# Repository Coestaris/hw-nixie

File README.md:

# Nixie clock

Both clock revisions and the tube docks have been manufactured and tested.

> **AI use.** The authors use AI for additional validation, component research, testbench setup and simulation, intermediate design reviews, release setup, and assistance with KiCad and 3D model edits. The authors developed the original designs and schematics manually, and other people reviewed them. The authors make the technical and visual decisions and take responsibility for them.

This USB-powered clock drives four IN-8-2 nixie tubes. Rev1 tests the boost converter. Rev2 combines the high-voltage supply, controller, and tube drivers on one motherboard. Each standalone dock carries one tube and plugs into Rev2.

## Goals and architecture

Rev1 isolates the high-voltage stage so its topology and control can be evaluated independently. An XL6007 and TDK ATB322524 transformer form the boost stage, with an MCP6001 in the control circuitry. The simulation sources document startup behavior and the limits of the behavioral models.

Rev2 adds an STM32U073 controller, four IN-8-2 docks, 74HC595 shift registers, ULN2003A arrays, and discrete high-voltage drivers. USB-C supplies the board. The MCU controls the display and the adjustable high-voltage supply.

```mermaid
flowchart LR
  USB[USB-C power] --> Boost[XL6007 high-voltage stage]
  USB --> Logic[Logic supply]
  Logic --> MCU[STM32U073]
  MCU --> Drivers[Shift registers and tube drivers]
  Boost --> Tubes[Four IN-8-2 tube docks]
  Drivers --> Tubes
  MCU --> Boost
```

## Hardware projects

| Board | Purpose | Design | Simulation |
| --- | --- | --- | --- |
| dock_rev1 | Tube carrier | [KiCad project](hardware/dock_rev1/dock_rev1.kicad_pro) | — |
| rev1 | Boost converter test board | [KiCad project](hardware/rev1/nixie_rev1.kicad_pro) | [Models, runner, and test cases](sim/rev1/) |
| rev2 | Four-tube clock motherboard | [KiCad project](hardware/rev2/nixie_rev2.kicad_pro) | [Models, runner, and test cases](sim/rev2/) |

### dock_rev1 - IN-8-2 dock

The two-layer dock carries one wire-ended IN-8-2 tube. Four 1×3, 2.54 mm sockets mate with the motherboard pin headers and carry the anode, digit cathodes, and decimal point. The assembly model includes the tube and all four sockets. [Dock release](https://github.com/Coestaris/hw-nixie/releases/tag/dock_rev1)

<details>
<summary>Top and bottom views</summary>

</details>

| File | Download |
| --- | --- |
| Schematic PDF | [dock_rev1-schematic.pdf](https://github.com/Coestaris/hw-nixie/releases/download/dock_rev1/dock_rev1-schematic.pdf) |
| PCB PDF | [dock_rev1-pcb.pdf](https://github.com/Coestaris/hw-nixie/releases/download/dock_rev1/dock_rev1-pcb.pdf) |
| Gerbers and drill files | [dock_rev1-gerbers.zip](https://github.com/Coestaris/hw-nixie/releases/download/dock_rev1/dock_rev1-gerbers.zip) |
| 3D assembly model | [dock_rev1.stpz](https://github.com/Coestaris/hw-nixie/releases/download/dock_rev1/dock_rev1.stpz) |

### rev1 - boost topology test board

Rev1 isolates the high-voltage converter and its control loop for bring-up. [Rev1 release](https://github.com/Coestaris/hw-nixie/releases/tag/rev1)

<details>
<summary>Top and bottom views</summary>

</details>

| File | Download |
| --- | --- |
| Schematic PDF | [nixie_rev1-schematic.pdf](https://github.com/Coestaris/hw-nixie/releases/download/rev1/nixie_rev1-schematic.pdf) |
| PCB PDF | [nixie_rev1-pcb.pdf](https://github.com/Coestaris/hw-nixie/releases/download/rev1/nixie_rev1-pcb.pdf) |
| Gerbers and drill files | [nixie_rev1-gerbers.zip](https://github.com/Coestaris/hw-nixie/releases/download/rev1/nixie_rev1-gerbers.zip) |
| JLCPCB BOM | [nixie_rev1-jlcpcb-bom.csv](https://github.com/Coestaris/hw-nixie/releases/download/rev1/nixie_rev1-jlcpcb-bom.csv) |
| JLCPCB placement | [nixie_rev1-jlcpcb-pnp.csv](https://github.com/Coestaris/hw-nixie/releases/download/rev1/nixie_rev1-jlcpcb-pnp.csv) |
| 3D assembly model | [nixie_rev1.stpz](https://github.com/Coestaris/hw-nixie/releases/download/rev1/nixie_rev1.stpz) |
| Simulation netlist, log, and results | [nixie_rev1-simulation.tar.gz](https://github.com/Coestaris/hw-nixie/releases/download/rev1/nixie_rev1-simulation.tar.gz) |

#### Hardware bring-up

The converter started normally, and the enable pin worked as expected. The bulk capacitor footprint limited the choice of high-voltage electrolytics. The only suitable part available for bring-up was a physically large 33 µF electrolytic, which replaced the 2.2 µF part specified in the schematic. The larger capacitance slowed the response to voltage adjustments.

#### Bench test results

- **Output voltage and ripple.** With a load equivalent to 20 kΩ (10 mA at 200 V), the output reached about 240–245 V with approximately 40–50 mV of ripple.
- **Voltage adjustment.** As the control setting increased, the output rose roughly linearly at first, then leveled off in a way that resembled an exponential approach to a limit. Under these test conditions, about 230 V was the practical upper limit for normal regulation.
- **Switching spikes.** At 245 V output, the measured spikes stayed at or below 40 V. This was considered acceptable for the transformer, so the prototype ran without a snubber.

<details>
<summary>Bring-up photos</summary>

</details>

### rev2 - clock motherboard

Rev2 supplies power and digit-drive signals to four plug-in docks. The assembly model includes the docks, their pin headers, and M2 standoffs. [Rev2 release](https://github.com/Coestaris/hw-nixie/releases/tag/rev2)

<details>
<summary>Top and bottom views</summary>

</details>

| File | Download |
| --- | --- |
| Schematic PDF | [nixie_rev2-schematic.pdf](https://github.com/Coestaris/hw-nixie/releases/download/rev2/nixie_rev2-schematic.pdf) |
| PCB PDF | [nixie_rev2-pcb.pdf](https://github.com/Coestaris/hw-nixie/releases/download/rev2/nixie_rev2-pcb.pdf) |
| Gerbers and drill files | [nixie_rev2-gerbers.zip](https://github.com/Coestaris/hw-nixie/releases/download/rev2/nixie_rev2-gerbers.zip) |
| JLCPCB BOM | [nixie_rev2-jlcpcb-bom.csv](https://github.com/Coestaris/hw-nixie/releases/download/rev2/nixie_rev2-jlcpcb-bom.csv) |
| JLCPCB placement | [nixie_rev2-jlcpcb-pnp.csv](https://github.com/Coestaris/hw-nixie/releases/download/rev2/nixie_rev2-jlcpcb-pnp.csv) |
| 3D assembly model | [nixie_rev2.stpz](https://github.com/Coestaris/hw-nixie/releases/download/rev2/nixie_rev2.stpz) |
| Simulation netlist, log, and results | [nixie_rev2-simulation.tar.gz](https://github.com/Coestaris/hw-nixie/releases/download/rev2/nixie_rev2-simulation.tar.gz) |

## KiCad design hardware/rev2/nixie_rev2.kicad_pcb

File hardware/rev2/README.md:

# Nixie clock — revision 2

This revision has a USB-powered 5 V boost supply and four IN-8-2 lamp docks. With `R3=62k`, `R4=5.1k`, and `R13=29.4k`, the nominal feedback equation gives 128.8–180.0 V for a 0–3.3 V DAC command. Component and reference tolerances can take the output beyond these endpoints; the resistor changes do not enforce a hard 180 V ceiling.

The only KiCad project is [`nixie_rev2.kicad_pro`](nixie_rev2.kicad_pro). Its schematic is PCB-linked and also contains the KiCad/ngspice model mappings, testbench includes, and default transient analysis. The [`../../sim/rev2`](../../sim/rev2) directory contains supporting behavioral models, run profiles, result notes, and analysis tools; it does not contain a second schematic or project copy.

## Current hardware state

- `N1`–`N4` use the project-local `nixie_rev2:IN-8-2_Dock` symbol and footprint. Each footprint reproduces the exact four diagonal 1×3, 2.54 mm header locations from the historical lamp-dock design; the inner lamp-solder pads remain part of the manufactured dock and are intentionally not duplicated on the motherboard.
- `Q1` uses the project-local `nixie_rev2:2N7002` symbol with KiCad's standard `Package_TO_SOT_SMD:SOT-23` footprint (`1=G`, `2=S`, `3=D`).
- `T1` is JLCPCB/LCSC `C249001`, TDK `ATB322524-0110-T000` (Extended, Production/NRND). It uses the project-local `nixie_rev2:ATB322524-0110-T000` symbol and datasheet-derived `nixie_rev2:TDK_ATB3225` footprint. Physical pins 1–4 are the primary and pins 2–3 are the secondary.
- `U1` is JLCPCB/LCSC `C5240411`, XLSEMI `XL6007E1`, using the matching 150-mil `SOIC-8_3.9x4.9mm_P1.27mm` footprint.
- `D3` is JLCPCB/LCSC `C84263`, NationStar `NCD0603R1`; its datasheet explicitly matches KiCad's pad-1-cathode LED polarity.
- `F1` is the 1206 resettable PTC JLCPCB/LCSC `C369161`, Jinrui `JK-nSMD100-16` (1 A hold, 16 V maximum).
- `R20`, `R25`, `R30`, and `R37` are 33 kΩ 1206 parts (`C137309`) feeding the digit anodes. `R38` is a 130 kΩ 1206 part (`C229306`) in the dot cathode path. At 180 V and the IN-8-2's 100 V keep-up voltage, nominal digit current is 2.42 mA and dot current is 0.49 mA. The digit resistor dissipates 0.194 W against its 0.25 W rating at 70 °C; a shorted tube exceeds that rating. The lamp may not ignite at the low end of the boost range.
- Simulation defaults are 5 V input, enable asserted at 1 ms, `MC_BOOST_CV=1.65 V`, and a 100 kΩ high-voltage load.
- The current 100 ms mid-scale startup simulation reaches about 156 V, near the 154.4 V feedback-equation target. Its modeled clamp reaches about 60.54 V. The simulation gate permits up to 65 V under an explicit 5 V user allowance; the physical XL6007 switch rating remains 60 V.

This revision has been manufactured. The following model limitations remain relevant. The TDK behavioral models remain suitable only for topology work, not efficiency or stress sign-off. Transformer polarity, saturation, winding capacitance, compensation, startup, component stress, and fault behavior still need bench verification. See [`../../sim/rev2/results/startup_midscale.md`](../../sim/rev2/results/startup_midscale.md).

## Mechanical assembly

N1–N4 each show the [dock STEP assembly](../../assets/Nixie/dock_rev1-assembly.stpz) seated on four straight 1×3, 2.54 mm male headers. The dock model has a Z offset of 11.125 mm from the Rev2 model mount plane. SolidCraft inspection of the assembled STEP confirmed the four header and socket row centers and the mating planes.

In KiCad’s 3D Viewer, enable **Show 3D Models not in POS File** (`P`) and **Show Unspecified 3D Models** (`V`) to display the mechanical references. [KiCad 3D Viewer controls](https://docs.kicad.org/10.0/en/pcbnew/pcbnew.html)

H1–H4 use [M2 × 12 female–female hex spacers](../../assets/Mechanical/Hex_Standoff_M2_L12.stpz) centered under the Ø2.2 mm mounting holes. The 12 mm length leaves 2.1 mm below the tallest modeled underside component. The [SolidCraft source](../../assets/Mechanical/Hex_Standoff_M2_L12.sc) recreates the 4 mm across-flats envelope and uses a simplified axial bore. The supplied `Spacer M2 F F 12mm.stp` from `spacers-m2-1.snapshot.3.zip` contained open surfaces. Its SHA-256 is `842bb0d11cc96b8b27d7705f7006af9b003dc60c31174bb7509f7d39eccfacad`.

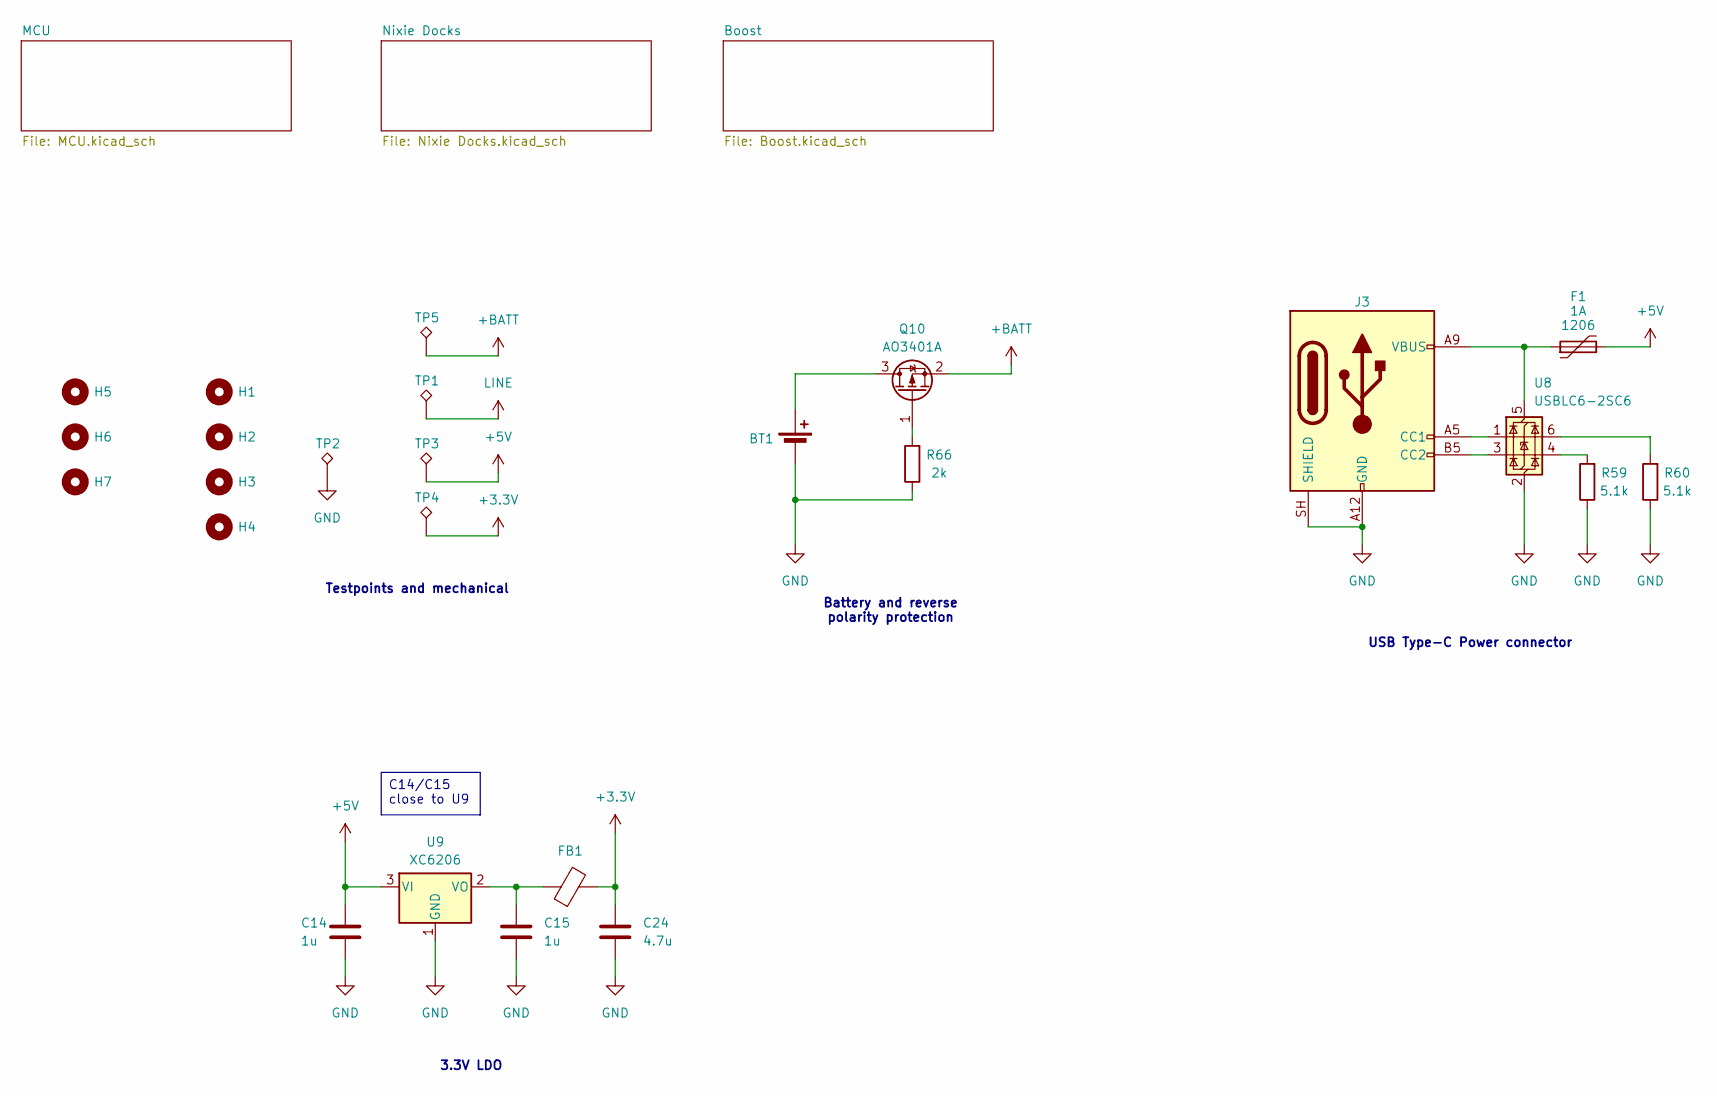
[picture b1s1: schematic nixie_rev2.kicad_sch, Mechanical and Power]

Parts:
BT1: Battery_Cell; XDCR-1220-006; Manufacturer Part Number XDCR-1220-006; LCSC Part # C7498147
C14, C15: 1u; C_0603_1608Metric; Manufacturer Part Number CC0603KRX7R6BB105; LCSC Part # C113807
C24: 4.7u; C_0603_1608Metric; Manufacturer Part Number CC0603KRX5R6BB475; LCSC Part # C109456
F1: 1A; Fuse_1206_3216Metric; Manufacturer Part Number JK-nSMD100-16; JLCPCB Part Type Extended
FB1: FerriteBead; L_0603_1608Metric; Manufacturer Part Number MPZ1608S601ATA00; LCSC Part # C107335
H1, H2, H3, H4: MountingHole; MountingHole_2.2mm_M2
H5, H6, H7: MountingHole; ToolingHole_1.152mm
J3: USB_C_Receptacle_PowerOnly_6P; USB_C_Receptacle_SHOU_HAN_TYPE-C_6P_073; Manufacturer Part Number TYPE-C 6P(073); LCSC Part # C668623
Q10: AO3401A; SOT-23; Manufacturer Part Number AO3401A; JLCPCB Part Type Basic
R59, R60: 5.1k; R_0201_0603Metric; Manufacturer Part Number RC0201JR-075K1L; LCSC Part # C163490
R66: 2k; R_0201_0603Metric; Manufacturer Part Number SC0201F2001G1BNRH; LCSC Part # C5140760
TP1, TP2, TP3, TP4, TP5: TestPoint_Alt; TestPoint_Pad_D1.0mm
U8: USBLC6-2SC6; SOT-23-6; Manufacturer Part Number USBLC6-2SC6; LCSC Part # C7519
U9: XC6206; SOT-23-3; Manufacturer Part Number XC6206P332MR; LCSC Part # C479053

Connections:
+3.3V: C24.1, FB1.2, TP4.1 (1_1); also elsewhere on the board
+5V: C14.1, F1.2, TP3.1 (1_1), U9.3 (VI); also elsewhere on the board
+BATT: Q10.2 (S), TP5.1 (1_1); also elsewhere on the board
GND: BT1.2 (-), C14.2, C15.2, C24.2, J3.A12 (GND), J3.B12 (GND), J3.SH (SHIELD), R59.1, R60.1, R66.1, TP2.1 (1_1), U8.2 (GND), U9.1 (GND); also elsewhere on the board
LINE: TP1.1 (1_1); also elsewhere on the board
unnamed: BT1.1 (+), Q10.3 (D)
unnamed: J3.A5 (CC1), U8.1 (I/O1)
unnamed: J3.B5 (CC2), U8.3 (I/O2)
unnamed: Q10.1 (G), R66.2
unnamed: R59.2, U8.4 (I/O2)
unnamed: R60.2, U8.6 (I/O1)
unnamed: F1.1, J3.A9 (VBUS), J3.B9 (VBUS), U8.5 (VBUS)
unnamed: C15.1, FB1.1, U9.2 (VO)

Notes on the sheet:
Testpoints and mechanical
3.3V LDO
USB Type-C Power connector
Battery and reverse polarity protection
C14/C15 close to U9

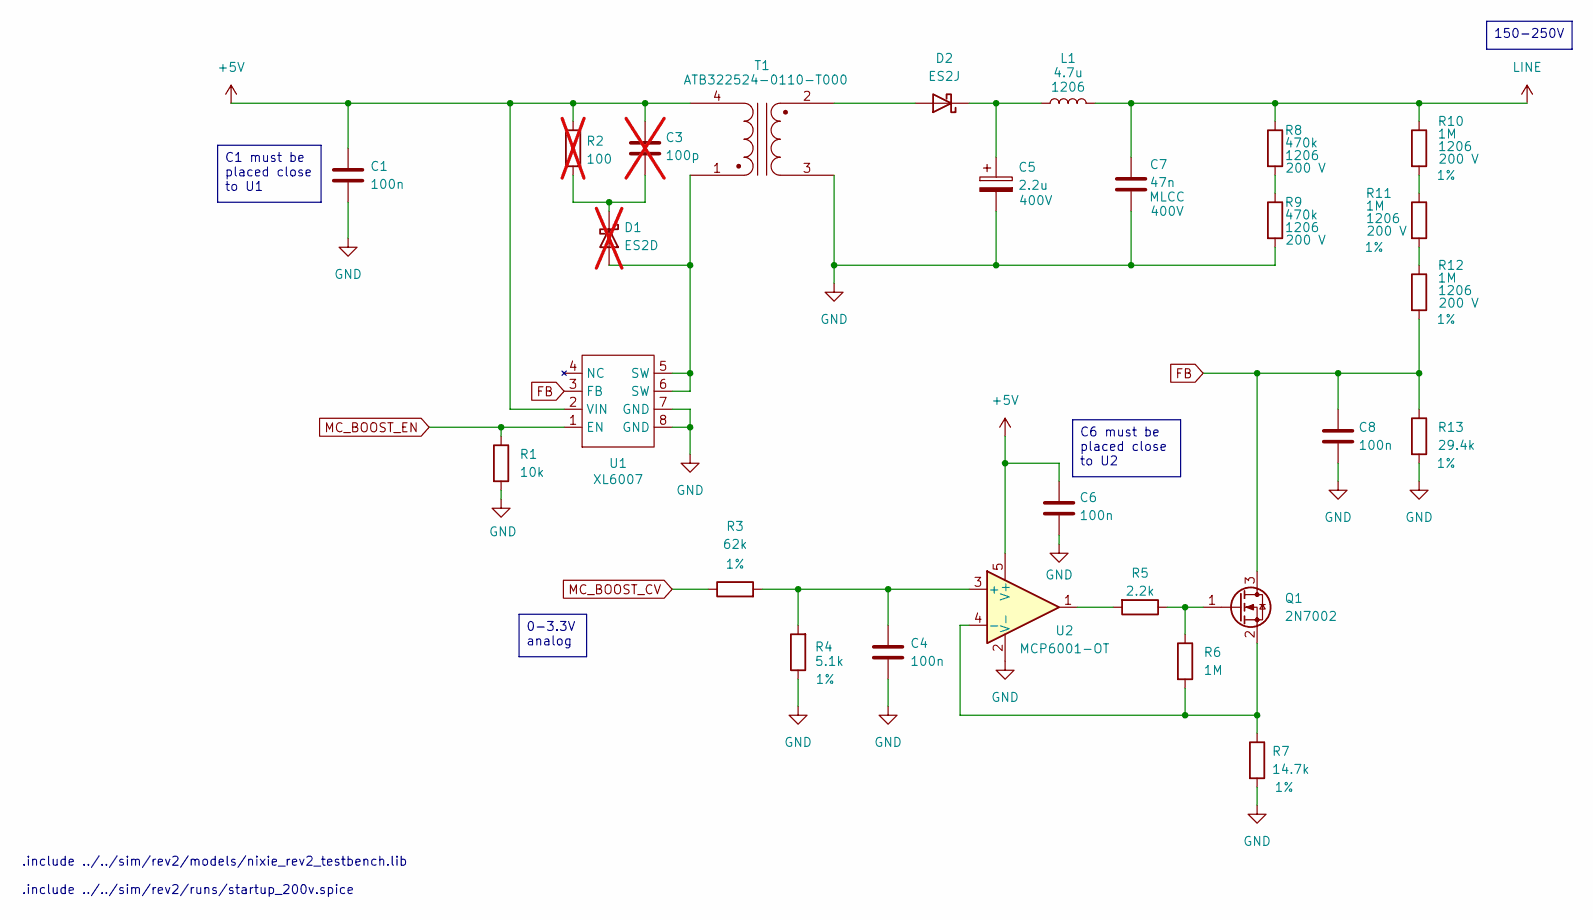
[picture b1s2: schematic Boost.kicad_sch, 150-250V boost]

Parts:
C1, C4, C6, C8: 100n; C_0201_0603Metric; Manufacturer Part Number TCC0201X7R104K100ZT; LCSC Part # C7393837
C3: 100p; C_0603_1608Metric; not fitted
C5: 2.2u; CP_Elec_6.3x9.9; Nominal Voltage 400V; Manufacturer Part Number UV2G2R2M0610; LCSC Part # C88684
C7: 47n; C_1206_3216Metric; Nominal Voltage 400V; Manufacturer Part Number TCC1206X7R473K501FT; LCSC Part # C309031
D1: ES2D; D_0603_1608Metric; not fitted
D2: ES2J; D_SMB; Manufacturer Part Number ES2JB; LCSC Part # C18199141
L1: 4.7u; L_1210_3225Metric; Manufacturer Part Number NLV32T-4R7J-EF; LCSC Part # C295128
Q1: 2N7002; SOT-23; Manufacturer Part Number 2N7002; LCSC Part # C8545
R1: 10k; R_0201_0603Metric; Manufacturer Part Number AF0201FR-0710KL; LCSC Part # C143978
R2: 100; R_0603_1608Metric; not fitted
R3: 62k; R_0201_0603Metric; Tolerance 1%; Manufacturer Part Number RC0201FR-0762KL; LCSC Part # C295812
R4: 5.1k; R_0201_0603Metric; Tolerance 1%; Manufacturer Part Number RC0201FR-075K1L; LCSC Part # C274341
R5: 2.2k; R_0201_0603Metric; Manufacturer Part Number RC0201FR-072K2L; LCSC Part # C142018
R6: 1M; R_0201_0603Metric; Manufacturer Part Number RC0201FR-071ML; LCSC Part # C295786
R7: 14.7k; R_0201_0603Metric; Tolerance 1%; Manufacturer Part Number RC0201DR-0714K7L; LCSC Part # C851654
R8, R9: 470k; R_1206_3216Metric; Nominal Voltage 200 V; Manufacturer Part Number RC1206FR-07470KL; LCSC Part # C137273
R10, R11, R12: 1M; R_1206_3216Metric; Nominal Voltage 200 V; Tolerance 1%; Manufacturer Part Number 1206W4F1004T5E; LCSC Part # C17927
R13: 29.4k; R_0603_1608Metric; Tolerance 1%; Manufacturer Part Number RC0603FR-0729K4L; LCSC Part # C137752
T1: ATB322524-0110-T000; TDK_ATB3225; Manufacturer Part Number ATB322524-0110-T000; LCSC Part # C249001
U1: XL6007; SOIC-8_3.9x4.9mm_P1.27mm; Manufacturer Part Number XL6007E1; LCSC Part # C5240411
U2: MCP6001-OT; SOT-23-5; Manufacturer Part Number MCP6001T-I/OT; LCSC Part # C116490

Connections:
+5V: C1.1, C3.1, C6.1, R2.1, T1.4 (P2), U1.2 (VIN), U2.5 (V+); also elsewhere on the board
FB: C8.1, Q1.3 (D), R12.2, R13.1, U1.3 (FB)
GND: C1.2, C4.1, C5.2, C6.2, C7.2, C8.2, R1.2, R4.1, R7.2, R9.2, R13.2, T1.3 (S2), U1.7 (GND), U1.8 (GND), U2.2 (V-); also elsewhere on the board
LINE: C7.1, L1.2, R8.1, R10.1; also elsewhere on the board
MC_BOOST_CV: R3.1; also elsewhere on the board
MC_BOOST_EN: R1.1, U1.1 (EN); also elsewhere on the board
unnamed: D1.2 (A), T1.1, U1.5 (SW), U1.6 (SW)
unnamed: C3.2, D1.1 (K), R2.2
unnamed: D2.2 (A), T1.2 (S1)
unnamed: C5.1, D2.1 (K), L1.1
unnamed: Q1.1 (G), R5.1, R6.1
unnamed: Q1.2 (S), R6.2, R7.1, U2.4 (-)
unnamed: R5.2, U2.1
unnamed: R8.2, R9.1
unnamed: R10.2, R11.1
unnamed: R11.2, R12.1
unnamed: C4.2, R3.2, R4.2, U2.3 (+)

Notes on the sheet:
.include ../../sim/rev2/models/nixie_rev2_testbench.lib
.include ../../sim/rev2/runs/startup_200v.spice
C6 must be placed close to U2
150-250V
C1 must be placed close to U1
0-3.3V analog

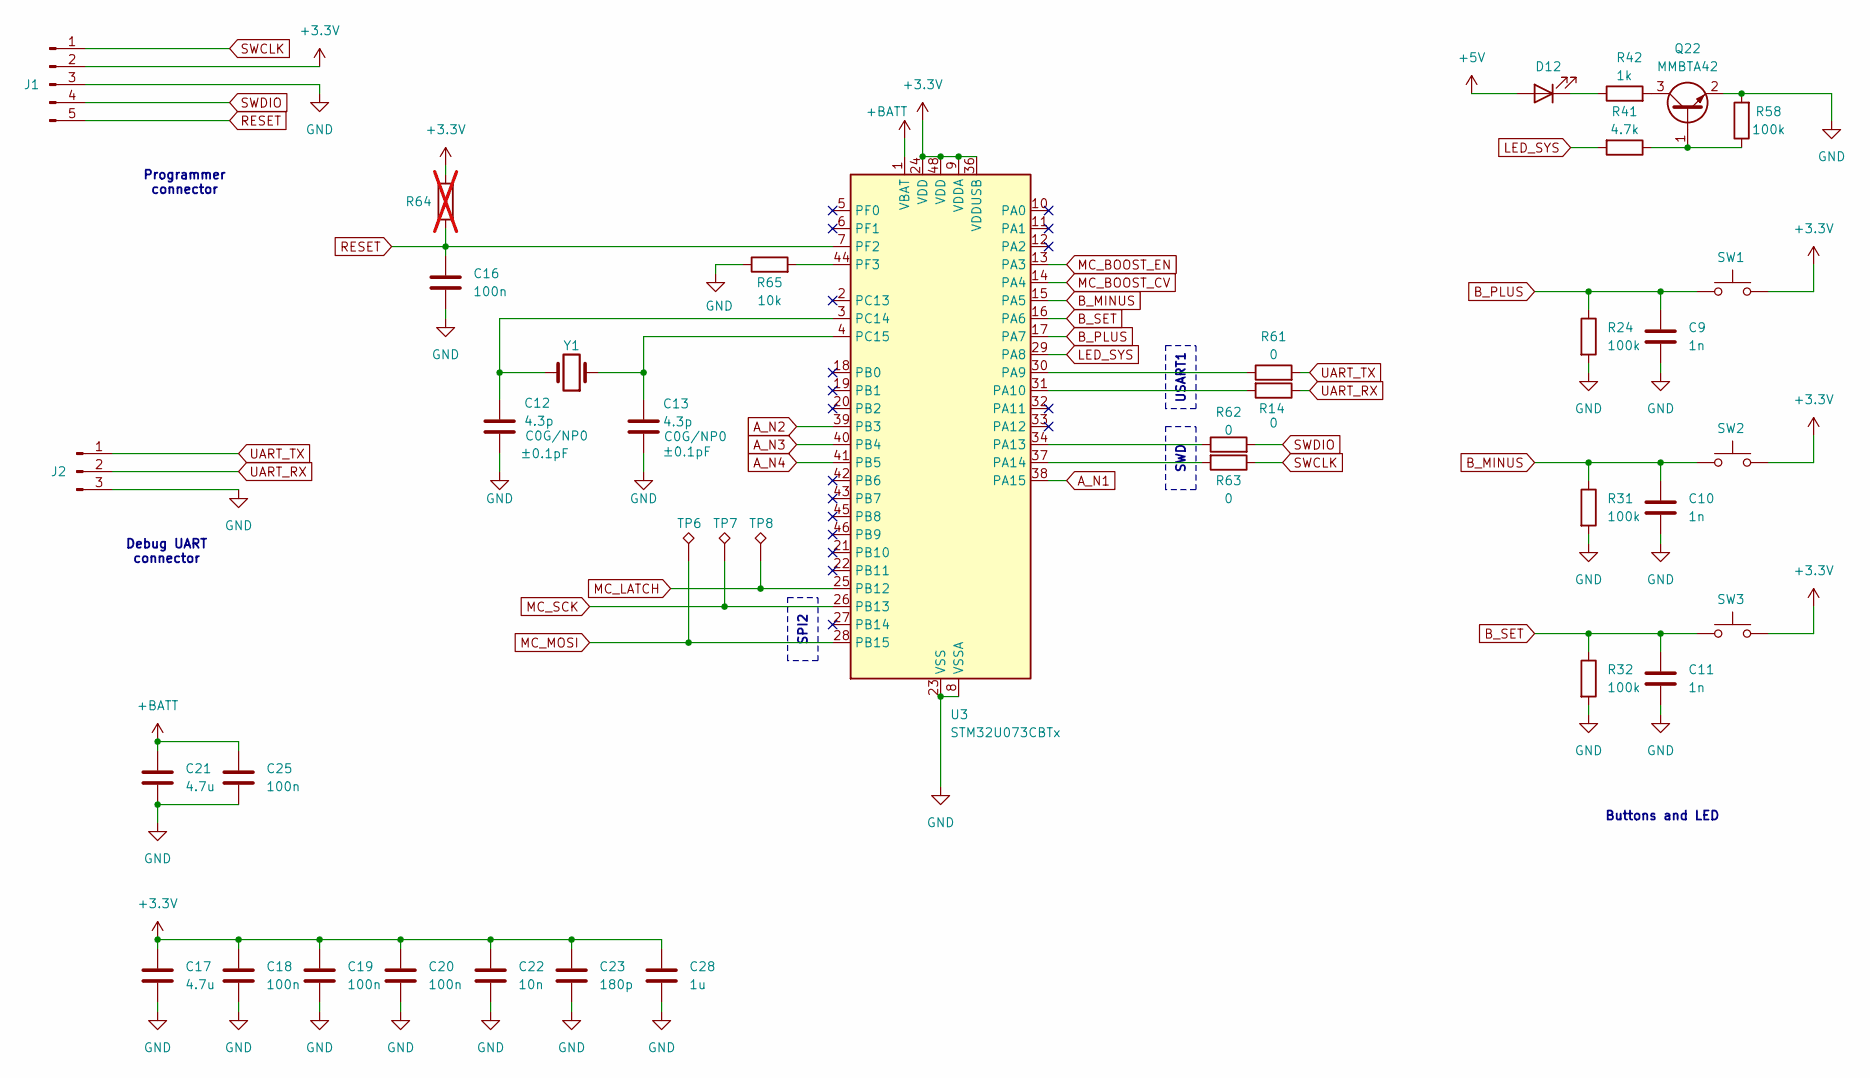
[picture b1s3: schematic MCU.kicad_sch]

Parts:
C9, C10, C11: 1n; C_0201_0603Metric; Manufacturer Part Number CC0201KRX7R9BB102; LCSC Part # C505464
C12, C13: 4.3p; C_0603_1608Metric; Tolerance ±0.1pF; Manufacturer Part Number CC0603BRNPO9BN4R3; LCSC Part # C519108
C16, C18, C19, C20, C25: 100n; C_0201_0603Metric; Manufacturer Part Number TCC0201X7R104K100ZT; LCSC Part # C7393837
C17, C21: 4.7u; C_0201_0603Metric; Manufacturer Part Number GRM035R60J475ME15D; LCSC Part # C335103
C22: 10n; C_0201_0603Metric; Manufacturer Part Number GRM033R61E103KA12D; LCSC Part # C76938
C23: 180p; C_0201_0603Metric; Manufacturer Part Number TCC0201COG181J500ZT; LCSC Part # C48986247
C28: 1u; C_0201_0603Metric; Manufacturer Part Number GRM033R61A105ME44D; LCSC Part # C76935
D12: LED; LED_0603_1608Metric; Manufacturer Part Number 19-21UYC/S530-A4/4T; LCSC Part # C2987536
J1: Conn_01x05_Pin; PinHeader_1x05_P1.27mm_Vertical
J2: Conn_01x03_Pin; PinHeader_1x03_P1.27mm_Vertical
Q22: MMBTA42; SOT-23; Manufacturer Part Number MMBTA42; LCSC Part # C50229541
R14, R61, R62, R63: 0; R_0201_0603Metric; Manufacturer Part Number RC0201JR-070RL; LCSC Part # C106228
R24, R31, R32, R58: 100k; R_0201_0603Metric; Manufacturer Part Number RC0201FR-07100KL; LCSC Part # C106224
R41: 4.7k; R_0201_0603Metric; Manufacturer Part Number RC0201FR-074K7L; LCSC Part # C138135
R42: 1k; R_0201_0603Metric; Manufacturer Part Number RTT011001FTH; LCSC Part # C102683
R64: 0; R_0201_0603Metric; Manufacturer Part Number RC0201JR-070RL; LCSC Part # C106228; not fitted
R65: 10k; R_0201_0603Metric; Manufacturer Part Number AF0201FR-0710KL; LCSC Part # C143978
SW1, SW2, SW3: SW_Push; SW_Push_1P1T_XKB_TS-1187A; Manufacturer Part Number TS-1187A-B-A-B; LCSC Part # C318884
TP6, TP7, TP8: TestPoint_Alt; TestPoint_Pad_D1.0mm
U3: STM32U073CBTx; LQFP-48_7x7mm_P0.5mm; Manufacturer Part Number STM32U073CBT6; LCSC Part # C27035627
Y1: NX3215SA-32.768K-STD-MUA-14; Crystal_SMD_3215-2Pin_3.2x1.5mm; Manufacturer Part Number NX3215SA-32.768K-STD-MUA-14; LCSC Part # C156244

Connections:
+3.3V: C17.1, C18.1, C19.1, C20.1, C22.1, C23.1, C28.1, J1.2, R64.2, SW1.2, SW2.2, SW3.2, U3.9 (VDDA), U3.24 (VDD), U3.36 (VDDUSB), U3.48 (VDD); also elsewhere on the board
+5V: D12.2 (A); also elsewhere on the board
+BATT: C21.1, C25.1, U3.1 (VBAT); also elsewhere on the board
A_N1: U3.38 (PA15); also elsewhere on the board
A_N2: U3.39 (PB3); also elsewhere on the board
A_N3: U3.40 (PB4); also elsewhere on the board
A_N4: U3.41 (PB5); also elsewhere on the board
B_MINUS: C10.1, R31.1, SW2.1, U3.15 (PA5)
B_PLUS: C9.1, R24.1, SW1.1, U3.17 (PA7)
B_SET: C11.1, R32.1, SW3.1, U3.16 (PA6)
GND: C9.2, C10.2, C11.2, C12.1, C13.1, C16.2, C17.2, C18.2, C19.2, C20.2, C21.2, C22.2, C23.2, C25.2, C28.2, J1.3, J2.3, Q22.2 (E), R24.2, R31.2, R32.2, R58.2, R65.1, U3.8 (VSSA), U3.23 (VSS), U3.35 (VSS), U3.47 (VSS); also elsewhere on the board
LED_SYS: R41.2, U3.29 (PA8)
MC_BOOST_CV: U3.14 (PA4); also elsewhere on the board
MC_BOOST_EN: U3.13 (PA3); also elsewhere on the board
MC_LATCH: TP8.1 (1_1), U3.25 (PB12); also elsewhere on the board
MC_MOSI: TP6.1 (1_1), U3.28 (PB15); also elsewhere on the board
MC_SCK: TP7.1 (1_1), U3.26 (PB13); also elsewhere on the board
unnamed: D12.1 (K), R42.1
unnamed: Q22.1 (B), R41.1, R58.1
unnamed: Q22.3 (C), R42.2
unnamed: R61.1, U3.30 (PA9)
unnamed: R14.2, U3.31 (PA10)
unnamed: R62.1, U3.34 (PA13)
unnamed: R63.2, U3.37 (PA14)
unnamed: C12.2, U3.3 (PC14), Y1.2
unnamed: C13.2, U3.4 (PC15), Y1.1
unnamed: R65.2, U3.44 (PF3)
RESET: C16.1, J1.5, R64.1, U3.7 (PF2)
SWCLK: J1.1, R63.1
SWDIO: J1.4, R62.2
UART_RX: J2.2, R14.1
UART_TX: J2.1, R61.2

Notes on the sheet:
Programmer connector
Buttons and LED
Debug UART connector
SWD
USART1
SPI2

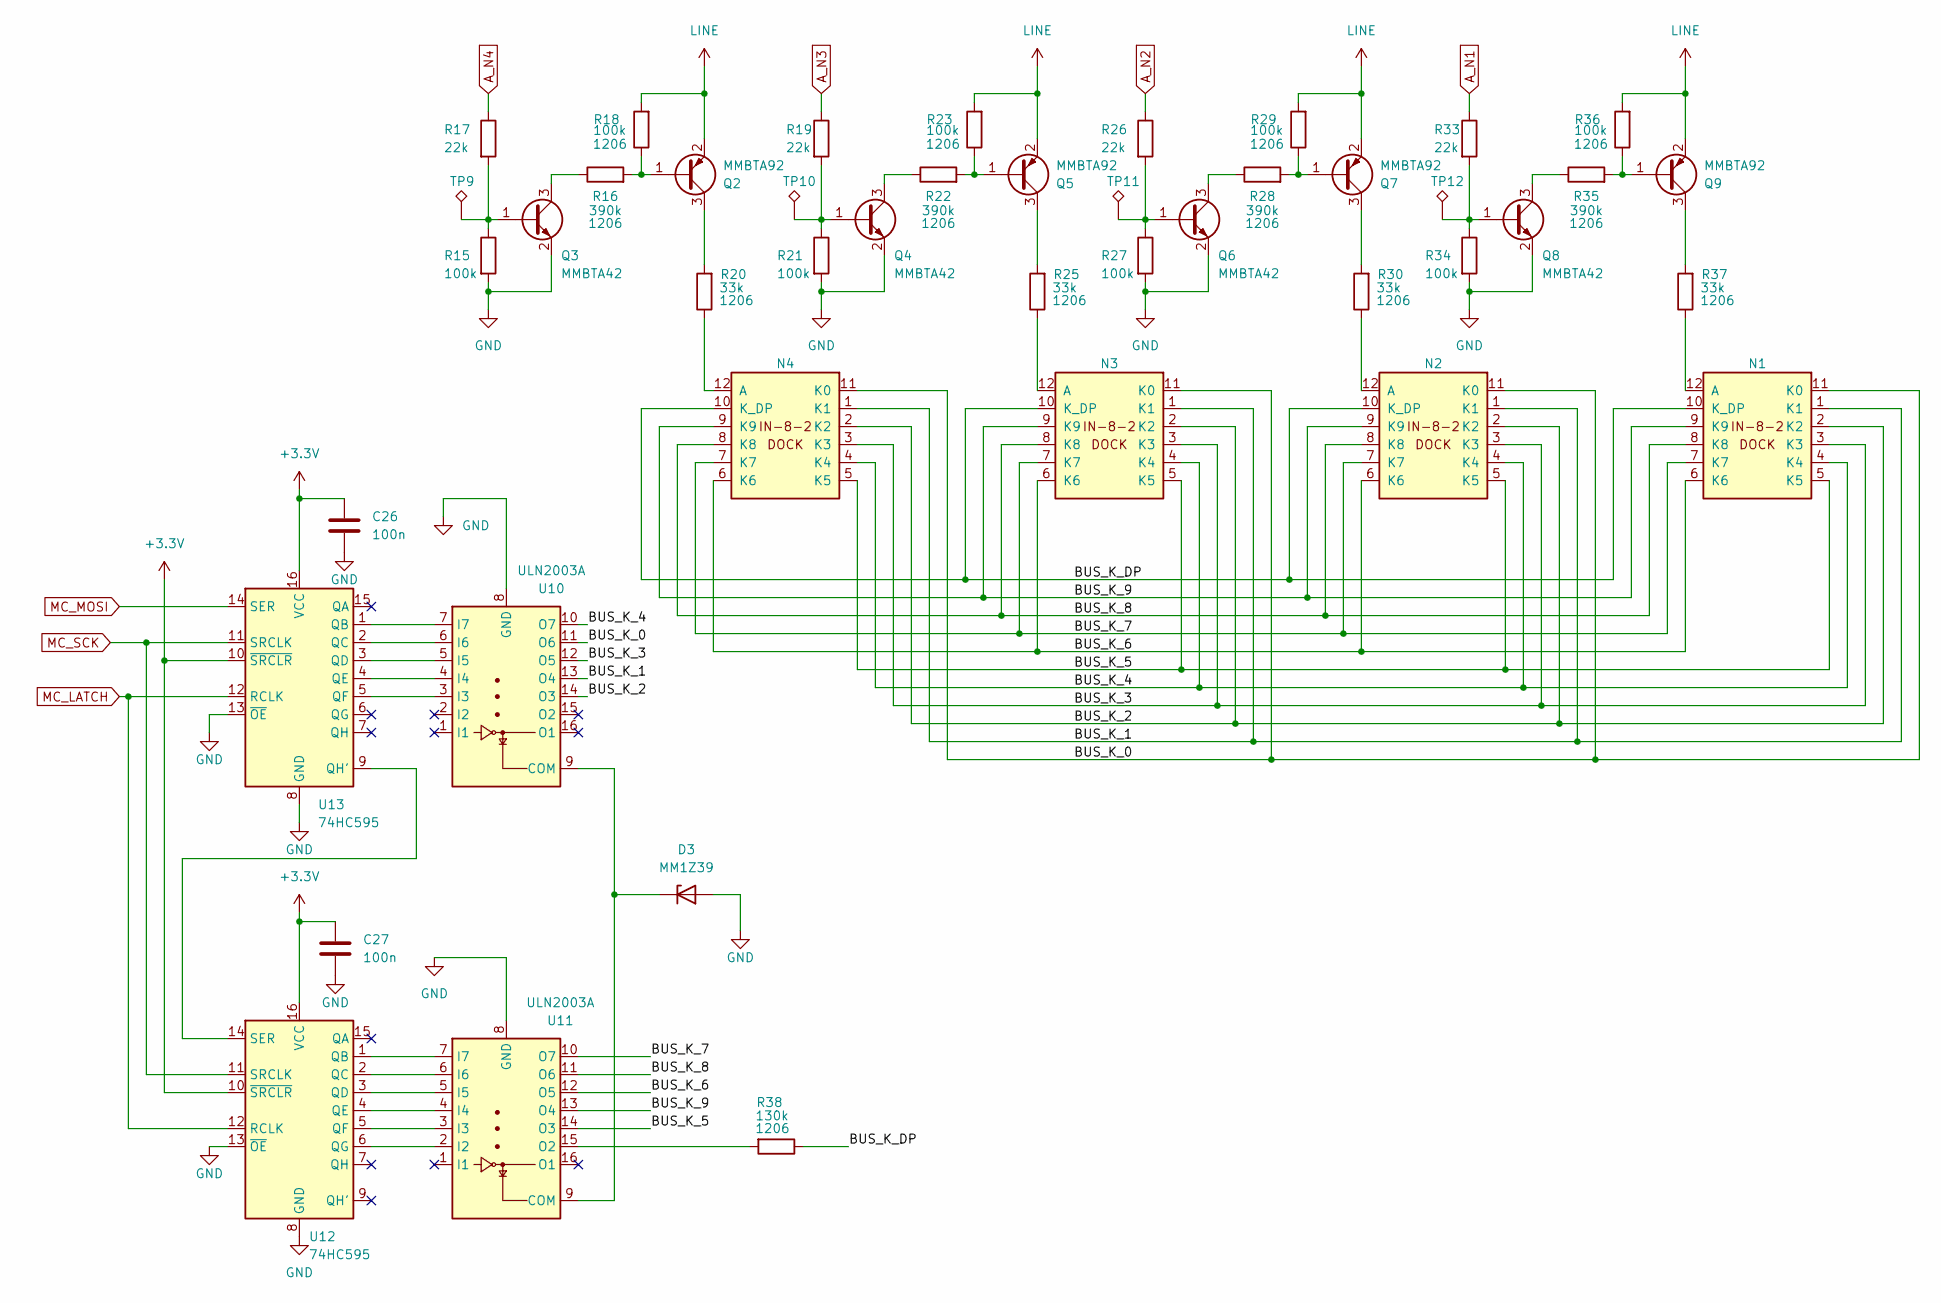
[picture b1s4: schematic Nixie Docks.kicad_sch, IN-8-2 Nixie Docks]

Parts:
C26, C27: 100n; C_0201_0603Metric; Manufacturer Part Number TCC0201X7R104K100ZT; LCSC Part # C7393837
D3: MM1Z39; D_SOD-123; Manufacturer Part Number MM1Z39; LCSC Part # C382788
N1, N2, N3, N4: IN-8-2_Dock
Q2, Q5, Q7, Q9: MMBTA92; SOT-23; Manufacturer Part Number MMBTA92; LCSC Part # C19184662
Q3, Q4, Q6, Q8: MMBTA42; SOT-23; Manufacturer Part Number MMBTA42; LCSC Part # C50229541
R15, R21, R27, R34: 100k; R_0201_0603Metric; Manufacturer Part Number RC0201FR-07100KL; LCSC Part # C106224
R16, R22, R28, R35: 390k; R_1206_3216Metric; Manufacturer Part Number 1206 ±1% 390K; LCSC Part # C2889679
R17, R19, R26, R33: 22k; R_0201_0603Metric; Manufacturer Part Number GR0201J22KTAG00; LCSC Part # C49653343
R18, R23, R29, R36: 100k; R_1206_3216Metric; Manufacturer Part Number SC1206F1003F8ANRH; LCSC Part # C3152242
R20, R25, R30, R37: 33k; R_1206_3216Metric; Manufacturer Part Number RC1206FR-0733KL; LCSC Part # C137309
R38: 130k; R_1206_3216Metric; Manufacturer Part Number AC1206FR-07130KL; LCSC Part # C229306
TP9, TP10, TP11, TP12: TestPoint_Alt; TestPoint_Pad_D1.0mm
U10, U11: ULN2003A; TSSOP-16_4.4x5mm_P0.65mm; Manufacturer Part Number ULN2003AIPWR(UMW); LCSC Part # C20617904
U12, U13: 74HC595; TSSOP-16_4.4x5mm_P0.65mm; Manufacturer Part Number 74HC595PW,118; LCSC Part # C5948

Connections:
+3.3V: C26.1, C27.1, U12.10 (~SRCLR), U12.16 (VCC), U13.10 (~SRCLR), U13.16 (VCC); also elsewhere on the board
/Nixie Docks/BUS_K_0: N1.11 (K0), N2.11 (K0), N3.11 (K0), N4.11 (K0), U10.11 (O6)
/Nixie Docks/BUS_K_1: N1.1 (K1), N2.1 (K1), N3.1 (K1), N4.1 (K1), U10.13 (O4)
/Nixie Docks/BUS_K_2: N1.2 (K2), N2.2 (K2), N3.2 (K2), N4.2 (K2), U10.14 (O3)
/Nixie Docks/BUS_K_3: N1.3 (K3), N2.3 (K3), N3.3 (K3), N4.3 (K3), U10.12 (O5)
/Nixie Docks/BUS_K_4: N1.4 (K4), N2.4 (K4), N3.4 (K4), N4.4 (K4), U10.10 (O7)
/Nixie Docks/BUS_K_5: N1.5 (K5), N2.5 (K5), N3.5 (K5), N4.5 (K5), U11.14 (O3)
/Nixie Docks/BUS_K_6: N1.6 (K6), N2.6 (K6), N3.6 (K6), N4.6 (K6), U11.12 (O5)
/Nixie Docks/BUS_K_7: N1.7 (K7), N2.7 (K7), N3.7 (K7), N4.7 (K7), U11.10 (O7)
/Nixie Docks/BUS_K_8: N1.8 (K8), N2.8 (K8), N3.8 (K8), N4.8 (K8), U11.11 (O6)
/Nixie Docks/BUS_K_9: N1.9 (K9), N2.9 (K9), N3.9 (K9), N4.9 (K9), U11.13 (O4)
/Nixie Docks/BUS_K_DP: N1.10 (K_DP), N2.10 (K_DP), N3.10 (K_DP), N4.10 (K_DP), R38.1
A_N1: R33.1; also elsewhere on the board
A_N2: R26.1; also elsewhere on the board
A_N3: R19.1; also elsewhere on the board
A_N4: R17.1; also elsewhere on the board
GND: C26.2, C27.2, D3.2 (A), Q3.2 (E), Q4.2 (E), Q6.2 (E), Q8.2 (E), R15.2, R21.2, R27.2, R34.2, U10.8 (GND), U11.8 (GND), U12.8 (GND), U12.13 (~OE), U13.8 (GND), U13.13 (~OE); also elsewhere on the board
LINE: Q2.2 (E), Q5.2 (E), Q7.2 (E), Q9.2 (E), R18.2, R23.2, R29.2, R36.2; also elsewhere on the board
MC_LATCH: U12.12 (RCLK), U13.12 (RCLK); also elsewhere on the board
MC_MOSI: U13.14 (SER); also elsewhere on the board
MC_SCK: U12.11 (SRCLK), U13.11 (SRCLK); also elsewhere on the board
unnamed: D3.1 (K), U10.9 (COM), U11.9 (COM)
unnamed: N1.12 (A), R37.1
unnamed: N2.12 (A), R30.1
unnamed: N3.12 (A), R25.1
unnamed: N4.12 (A), R20.1
unnamed: Q2.1 (B), R16.2, R18.1
unnamed: Q2.3 (C), R20.2
unnamed: Q3.1 (B), R15.1, R17.2, TP9.1 (1_1)
unnamed: Q3.3 (C), R16.1
unnamed: Q4.1 (B), R19.2, R21.1, TP10.1 (1_1)
unnamed: Q4.3 (C), R22.1
unnamed: Q5.1 (B), R22.2, R23.1
unnamed: Q5.3 (C), R25.2
unnamed: Q6.1 (B), R26.2, R27.1, TP11.1 (1_1)
unnamed: Q6.3 (C), R28.1
unnamed: Q7.1 (B), R28.2, R29.1
unnamed: Q7.3 (C), R30.2
unnamed: Q8.1 (B), R33.2, R34.1, TP12.1 (1_1)
unnamed: Q8.3 (C), R35.1
unnamed: Q9.1 (B), R35.2, R36.1
unnamed: Q9.3 (C), R37.2
unnamed: U10.3 (I3), U13.5 (QF)
unnamed: U10.4 (I4), U13.4 (QE)
unnamed: U10.5 (I5), U13.3 (QD)
unnamed: U10.6 (I6), U13.2 (QC)
unnamed: U10.7 (I7), U13.1 (QB)
unnamed: U11.2 (I2), U12.6 (QG)
unnamed: U11.3 (I3), U12.5 (QF)
unnamed: U11.4 (I4), U12.4 (QE)
unnamed: U11.5 (I5), U12.3 (QD)
unnamed: U11.6 (I6), U12.2 (QC)
unnamed: U11.7 (I7), U12.1 (QB)
unnamed: R38.2, U11.15 (O2)
unnamed: U12.14 (SER), U13.9 (QH')

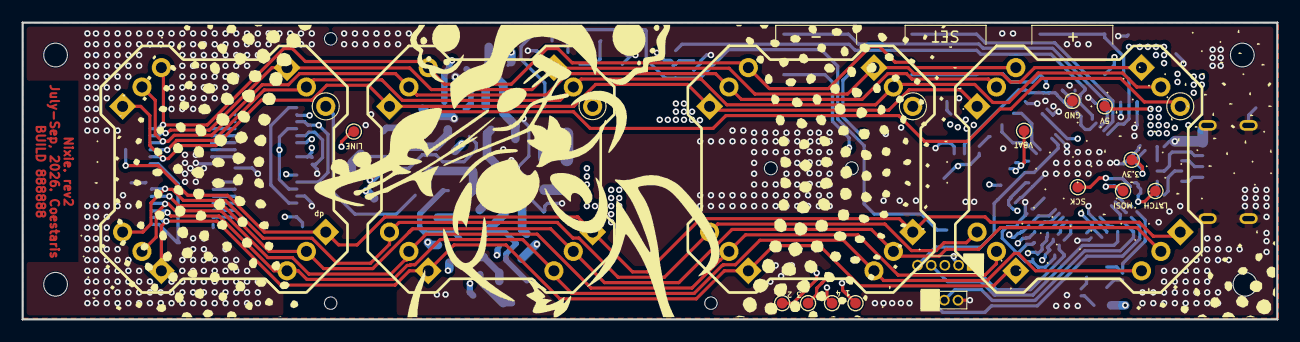
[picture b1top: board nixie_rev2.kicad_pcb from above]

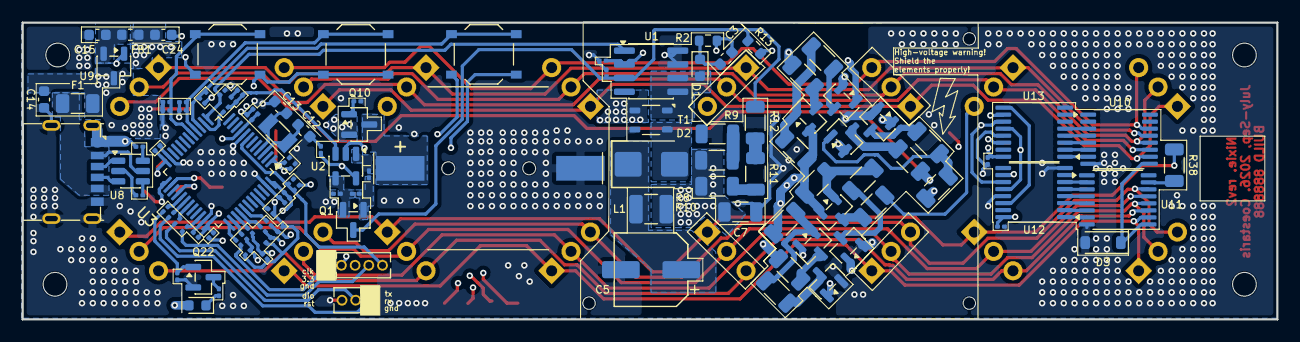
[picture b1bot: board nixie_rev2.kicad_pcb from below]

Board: 6 copper layers, 116.3 x 27.5 mm, 135 parts (116 on the bottom side), 98 nets.

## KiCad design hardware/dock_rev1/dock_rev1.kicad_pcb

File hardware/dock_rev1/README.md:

# IN-8-2 Nixie Dock, revision 1

This two-layer adapter carries one wire-ended IN-8-2 tube and plugs into a Rev2 clock motherboard. The tube mounts on the front, with four 1×3, 2.54 mm female sockets on the back. The motherboard supplies the high-voltage drive and current limiting. Open [dock_rev1.kicad_pro](dock_rev1.kicad_pro) in KiCad 10.

The outline and pad centers come from `projects/legacy/nixie/hardware/nixie.kicad_pcb` in `Coestaris/hardware-legacy` at `8a1bb16d6e56aa4d5cadc9abd9d31d0f6d3bca59`. Silkscreen rings identify the anode at the lamp and socket. The tube footprint uses the manufacturer's positions 2 through 13. The routes for the decimal point and digits 8 and 9 follow the tube passport while preserving the Rev2 motherboard pin assignments. [IN-8-2 manufacturer passport, page 2](../../assets/Nixie/IN-8-2.pdf)

The positions below are viewed from the tube side with the gap in the lamp pin circle at the top. Square pads mark socket pin 1.

| Socket | Position | Pin 1 | Pin 2 | Pin 3 |
| --- | --- | --- | --- | --- |
| J1 | Lower right | Decimal point | Digit 9 | Digit 8 |
| J2 | Lower left | Digit 7 | Digit 6 | Digit 5 |
| J3 | Upper left | Digit 4 | Digit 3 | Digit 2 |
| J4 | Upper right | Digit 1 | Digit 0 | Anode |

The lamp's [SolidCraft source](../../assets/Nixie/IN-8-2.sc) uses the documented maximum bulb envelope and the twelve legacy drill centers. Lead diameter, trimming, and bulb standoff are modeling assumptions. The supplied SolidWorks file could not be imported. The [model check](../../assets/Nixie/IN-8-2-qa.json) records the assumptions and verifies every lead against its plated hole. Physical fit and powered operation remain unverified.

The dock mounts four [1×3, 2.54 mm female sockets](../../assets/Connector_IDC/PinSocket_1x03_P2.54mm_Vertical.stpz) on J1–J4. They mate with four [1×3, 2.54 mm male headers](../../assets/Connector_IDC/PinHeader_1x03_P2.54mm_Vertical.stpz) on the motherboard. Both models come from the KiCad 10.0.8 3D libraries. [KiCad library license](https://www.kicad.org/libraries/license/)

The [dock assembly model](../../assets/Nixie/dock_rev1-assembly.stpz) contains the PCB, tube, and all four sockets. Its STEP origin is the tube footprint center at PCB coordinates `(76.173974, 65.570025)` mm. Rev2 uses this origin to place each dock over its 12 header pads.

## Release status

The GitHub Action target is `dock` and the release tag is `dock_rev1`. The [JLCPCB fabrication-only profile](../../assets/manufacturing/dock_rev1.yaml) selects the board, drill, drawing, and 3D artifacts for this hand-assembled design. KiCad ERC and DRC with schematic parity reported zero findings.

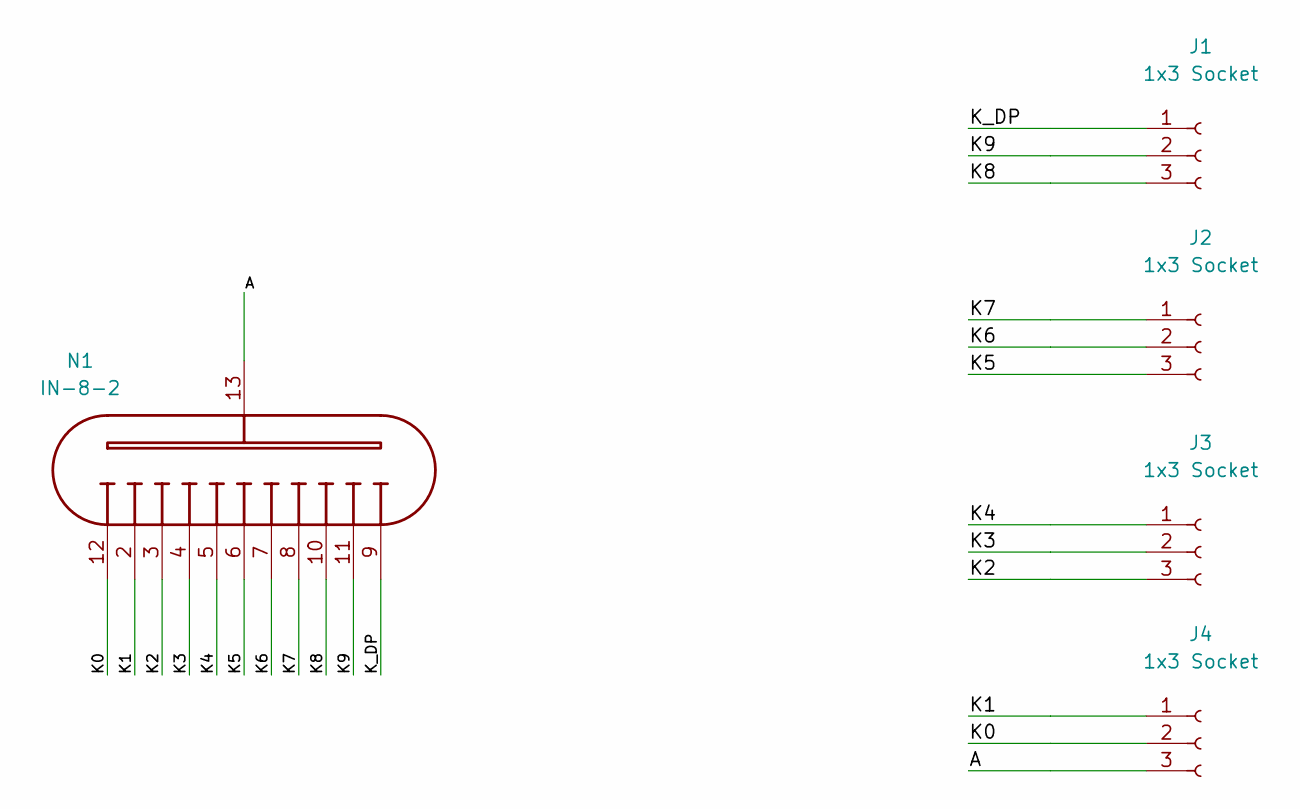
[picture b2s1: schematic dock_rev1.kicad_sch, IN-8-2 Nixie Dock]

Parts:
J1, J2, J3, J4: 1x3 Socket; Socket_1x03_P2.54mm
N1: IN-8-2

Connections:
/A: J4.3, N1.13 (A)
/K0: J4.2, N1.12 (K0)
/K1: J4.1, N1.2 (K1)
/K2: J3.3, N1.3 (K2)
/K3: J3.2, N1.4 (K3)
/K4: J3.1, N1.5 (K4)
/K5: J2.3, N1.6 (K5)
/K6: J2.2, N1.7 (K6)
/K7: J2.1, N1.8 (K7)
/K8: J1.3, N1.10 (K8)
/K9: J1.2, N1.11 (K9)
/K_DP: J1.1, N1.9 (K_DP)

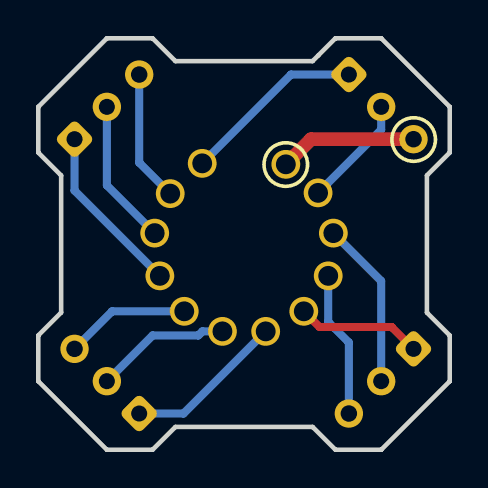
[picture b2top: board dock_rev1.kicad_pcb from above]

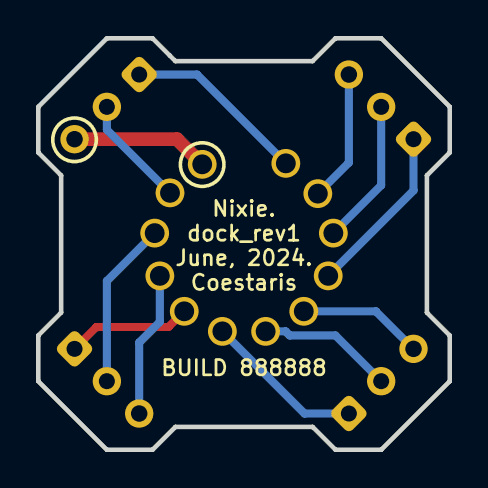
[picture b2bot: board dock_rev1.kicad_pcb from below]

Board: 2 copper layers, 22.9 x 22.9 mm, 5 parts (4 on the bottom side), 12 nets.
